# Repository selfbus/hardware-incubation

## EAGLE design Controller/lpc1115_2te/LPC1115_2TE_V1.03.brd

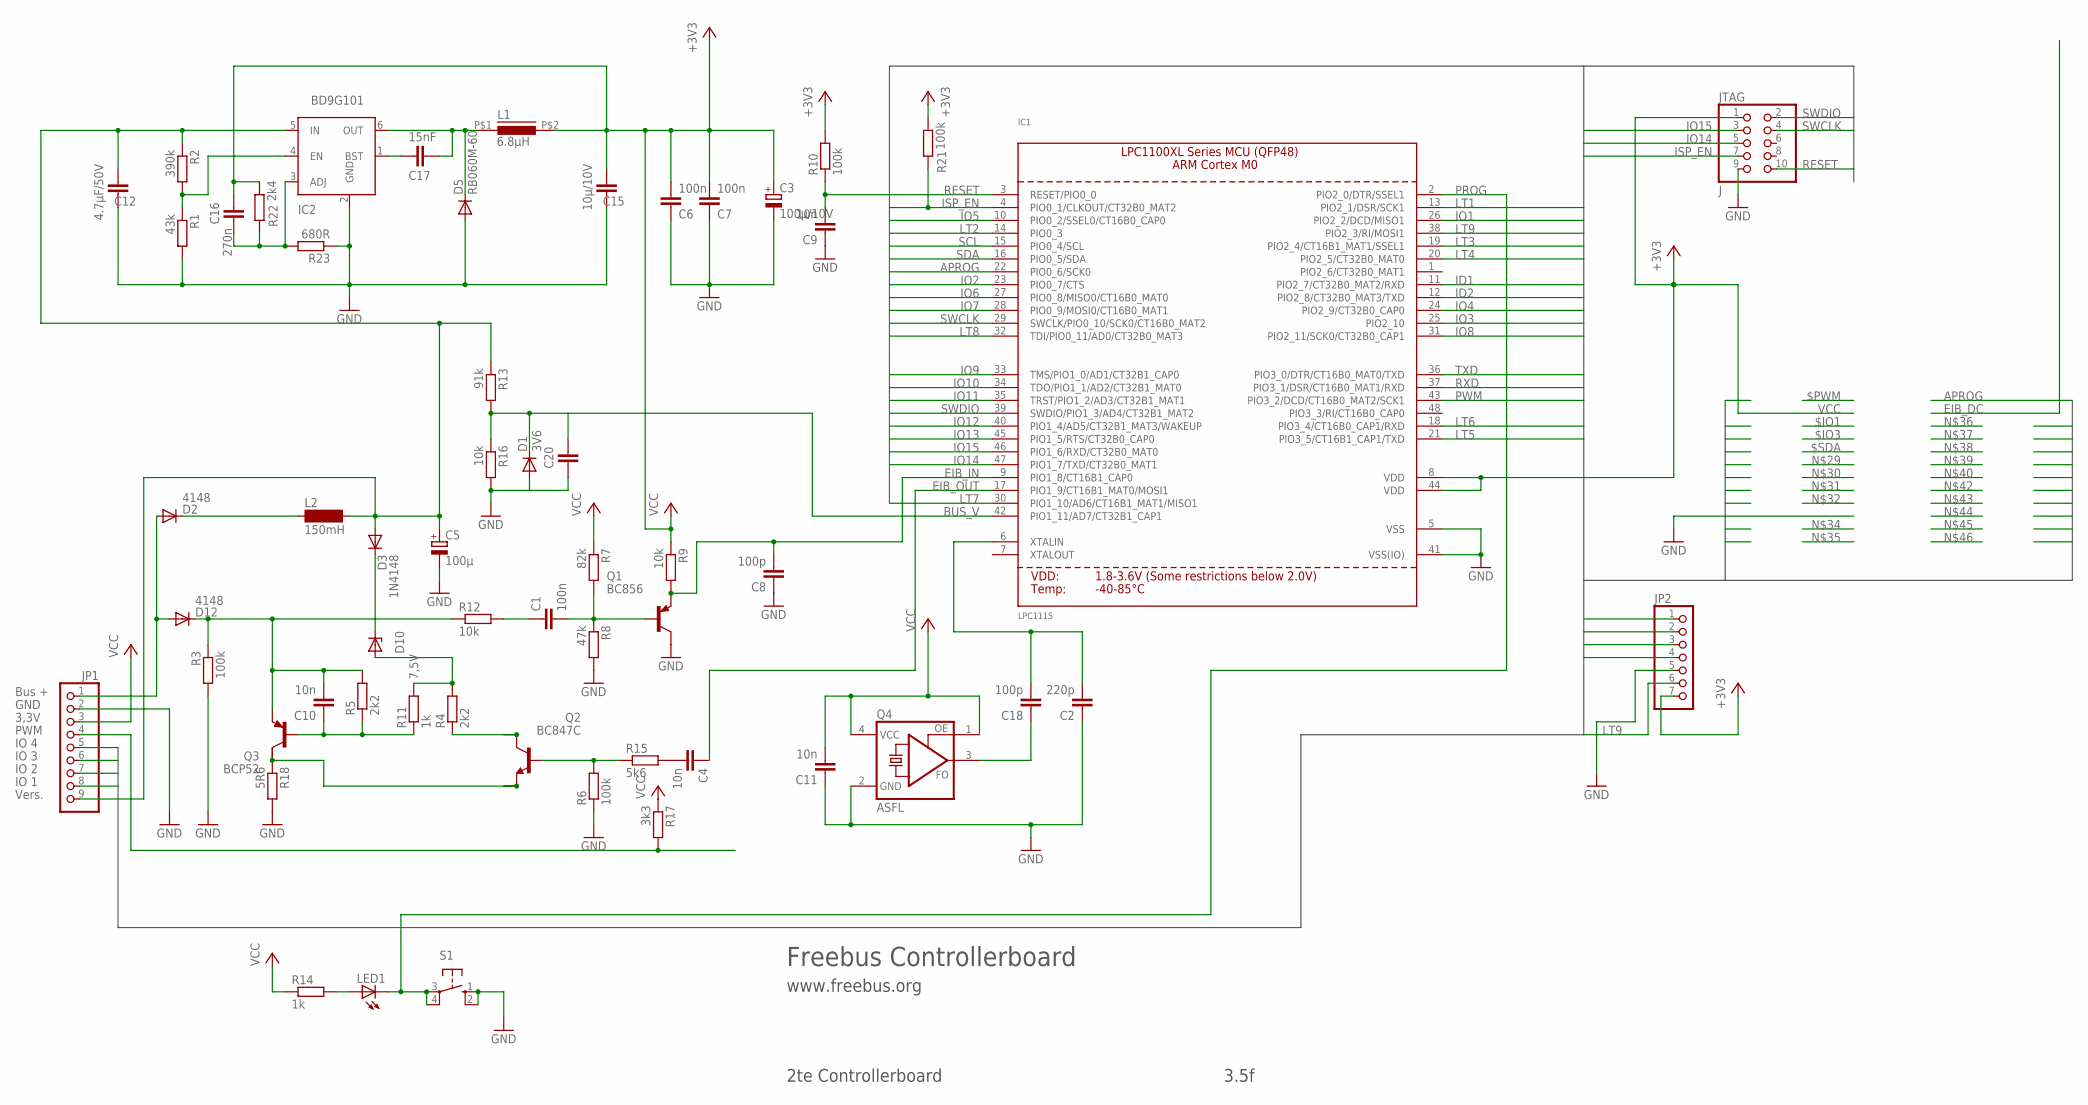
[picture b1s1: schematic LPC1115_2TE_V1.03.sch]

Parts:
C1, C6, C7: 100n; C1206
C2: 220p; C1206
C3: 100µ/10V; E2,5-5
C4, C10, C11: 10n; C1206
C5: 100µ; E3,5-8
C8: 100p; C1206K
C9: 10n; C1206K
C12: 4.7µF/50V; C1206K
C15: 10µ/10V; C1206K
C16: 270n; C1206
C17: 15nF; C1206
C18: 100p; C1206
C20: C-EUC1206; C1206
D1: 3V6; MINIMELF
D2, D12: 4148; MINIMELF
D3: 1N4148; MINIMELF
D5: RB060M-60; SOD123
D10: 7,5V; MINIMELF
IC1: LPC1115; LQFP48
IC2: BD9G101; SOT23-6
JP1: PINHD-1X9; 1X09
JP2: PINHD-1X7; 1X07
JTAG: J; 2X05M
L1: 6.8µH; PIS2812
L2: 150mH; BS11
LED1: LED3MM
Q1: BC856; SOT23-BEC
Q2: BC847C; SOT23
Q3: BCP52; SOT223
Q4: ASFL; ASF
R1: 43k; R1206
R2: 390k; R1206
R3, R6, R10, R21: 100k; R1206
R4, R5: 2k2; R1206
R7: 82k; R1206
R8: 47k; R1206
R9, R12, R16: 10k; R1206
R11, R14: 1k; R1206
R13: 91k; R1206
R15: 5k6; R1206
R17: 3k3; R1206
R18: 5R6; R1206
R22: 2k4; R1206
R23: 680R; R1206
S1: 10-XX; B3F-10XX

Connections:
APROG: IC1.22 (PIO0_6/SCK0), JP1.8
BASE: C1.2, Q1.B, R7.2, R8.1
BASE_SEND: Q2.1 (B), R6.2, R15.1
BUS_V: C20.2, D1.C, IC1.42 (PIO1_11/AD7/CT32B1_CAP1), R13.2, R16.1
EIB+: D2.A, D12.A, JP1.1
EIB_DC: C5.+, C12.2, D3.A, IC2.5 (IN), JP1.9, L2.2, R2.1, R13.1
EIB_IN: C8.2, IC1.9 (PIO1_8/CT16B1_CAP0), Q1.E, R9.2
EIB_OUT: C4.1, IC1.17 (PIO1_9/CT16B1_MAT0/MOSI1)
GND: C2.1, C3.-, C5.-, C6.1, C7.1, C8.1, C9.1, C11.1, C12.1, C15.1, C20.1, D1.A, D5.A, IC1.5 (VSS), IC1.41 (VSS(IO)), IC2.2 (GND), JP1.2, JP2.5, JTAG.9, Q1.C, Q4.2 (GND), R1.2, R3.2, R6.1, R8.2, R16.2, R18.2, R23.1, S1.1 (S), S1.2 (S1)
ID1: IC1.11 (PIO2_7/CT32B0_MAT2/RXD)
ID2: IC1.12 (PIO2_8/CT32B0_MAT3/TXD)
IO1: IC1.26 (PIO2_2/DCD/MISO1)
IO2: IC1.23 (PIO0_7/CTS)
IO3: IC1.25 (PIO2_10)
IO4: IC1.24 (PIO2_9/CT32B0_CAP0), JP1.5
IO5: IC1.10 (PIO0_2/SSEL0/CT16B0_CAP0)
IO6: IC1.27 (PIO0_8/MISO0/CT16B0_MAT0)
IO7: IC1.28 (PIO0_9/MOSI0/CT16B0_MAT1), JP1.7
IO8: IC1.31 (PIO2_11/SCK0/CT32B0_CAP1), JP1.6
IO9: IC1.33 (TMS/PIO1_0/AD1/CT32B1_CAP0)
IO10: IC1.34 (TDO/PIO1_1/AD2/CT32B1_MAT0)
IO11: IC1.35 (TRST/PIO1_2/AD3/CT32B1_MAT1)
IO12: IC1.40 (PIO1_4/AD5/CT32B1_MAT3/WAKEUP)
IO13: IC1.45 (PIO1_5/RTS/CT32B0_CAP0)
IO14: IC1.47 (PIO1_7/TXD/CT32B0_MAT1), JTAG.5
IO15: IC1.46 (PIO1_6/RXD/CT32B0_MAT0), JTAG.3
ISP_EN: IC1.4 (PIO0_1/CLKOUT/CT32B0_MAT2), JTAG.7, R21.1
I_SENSE: Q2.2 (E), Q3.2 (C), R18.1
LT1: IC1.13 (PIO2_1/DSR/SCK1)
LT2: IC1.14 (PIO0_3)
LT3: IC1.19 (PIO2_4/CT16B1_MAT1/SSEL1)
LT4: IC1.20 (PIO2_5/CT32B0_MAT0)
LT5: IC1.21 (PIO3_5/CT16B1_CAP1/TXD), JP2.1
LT6: IC1.18 (PIO3_4/CT16B0_CAP1/RXD), JP2.2
LT7: IC1.30 (PIO1_10/AD6/CT16B1_MAT1/MISO1), JP2.3
LT8: IC1.32 (TDI/PIO0_11/AD0/CT32B0_MAT3), JP2.4
LT9: IC1.38 (PIO2_3/RI/MOSI1), JP2.6
LX: C17.1, D5.C, IC2.6 (OUT), L1.P$1 (1)
unnamed: Q2.3 (C), R4.1
unnamed: C2.2, C18.2, IC1.6 (XTALIN)
unnamed: C10.2, D12.C, Q3.3 (E), R3.1, R5.2, R12.1
unnamed: C18.1, Q4.3 (FO)
unnamed: LED1.A, R14.2
unnamed: D2.C, L2.1
unnamed: D3.C, D10.C
unnamed: C1.1, R12.2
unnamed: C4.2, R15.2
unnamed: C17.2, IC2.1 (BST)
unnamed: IC2.4 (EN), R1.1, R2.2
unnamed: C16.1, IC2.3 (ADJ), R22.1, R23.2
unnamed: C10.1, Q3.1 (B), R5.1, R11.1
PROG: IC1.2 (PIO2_0/DTR/SSEL1), LED1.K (C), S1.3, S1.4 (P1)
PWM: IC1.43 (PIO3_2/DCD/CT16B0_MAT2/SCK1), JP1.4, R17.2
REFERENZ: D10.A, R4.2, R11.2
RESET: C9.2, IC1.3 (RESET/PIO0_0), JTAG.10, R10.1
RXD: IC1.37 (PIO3_1/DSR/CT16B0_MAT1/RXD)
SCL: IC1.15 (PIO0_4/SCL)
SDA: IC1.16 (PIO0_5/SDA)
SWCLK: IC1.29 (SWCLK/PIO0_10/SCK0/CT16B0_MAT2), JTAG.4
SWDIO: IC1.39 (SWDIO/PIO1_3/AD4/CT32B1_MAT2), JTAG.2
TXD: IC1.36 (PIO3_0/DTR/CT16B0_MAT0/TXD)
VCC: C3.+, C6.2, C7.2, C11.2, C15.2, C16.2, IC1.8 (VDD), IC1.44 (VDD), JP1.3, JP2.7, JTAG.1, L1.P$2 (2), Q4.1 (OE), Q4.4 (VCC), R7.1, R9.1, R10.2, R14.1, R17.1, R21.2, R22.2

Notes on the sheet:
Bus +
GND
3,3V
PWM
IO 1
IO 2
IO 3
IO 4
Vers.
Freebus Controllerboard
www.freebus.org
2te Controllerboard
3.5f

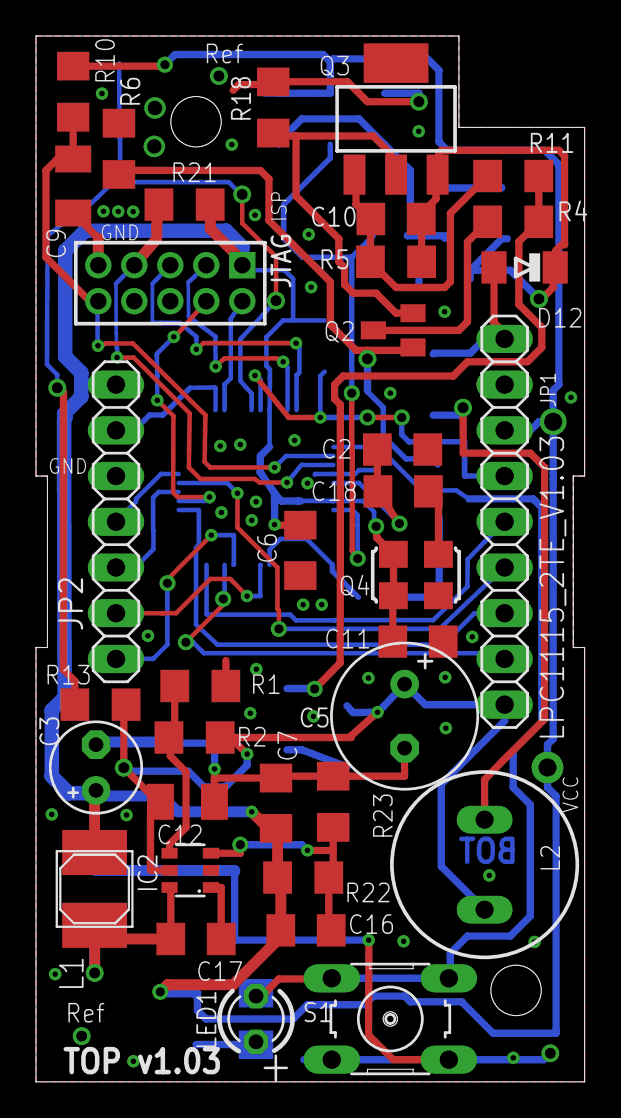
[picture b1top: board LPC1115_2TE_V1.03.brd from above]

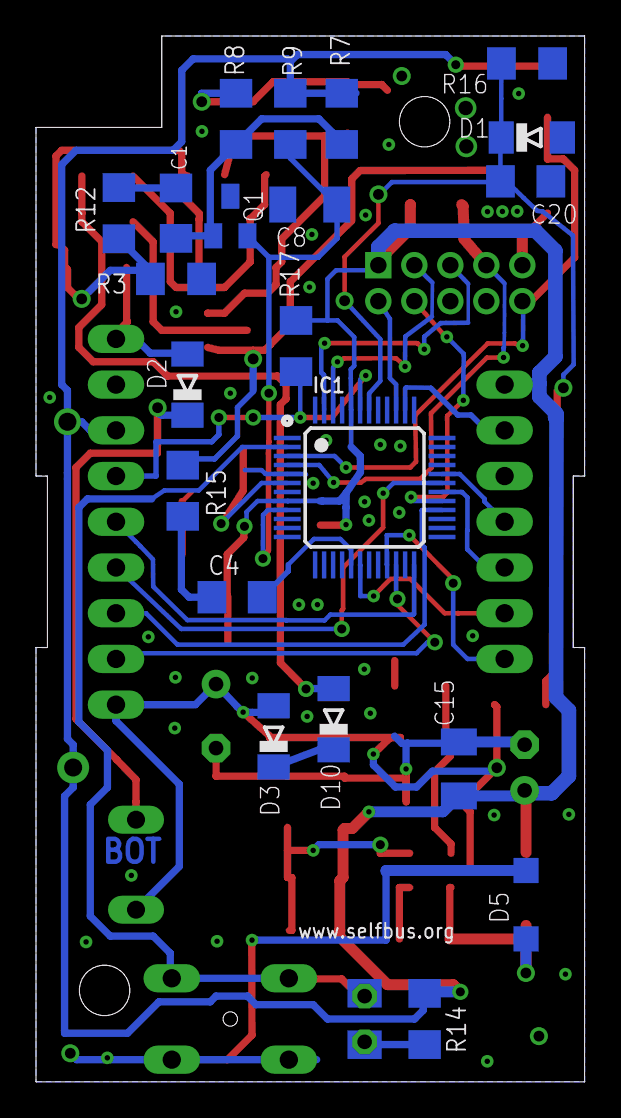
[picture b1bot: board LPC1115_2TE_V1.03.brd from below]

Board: 2 copper layers, 30.5 x 58.1 mm, 57 parts (21 on the bottom side), 42 nets.

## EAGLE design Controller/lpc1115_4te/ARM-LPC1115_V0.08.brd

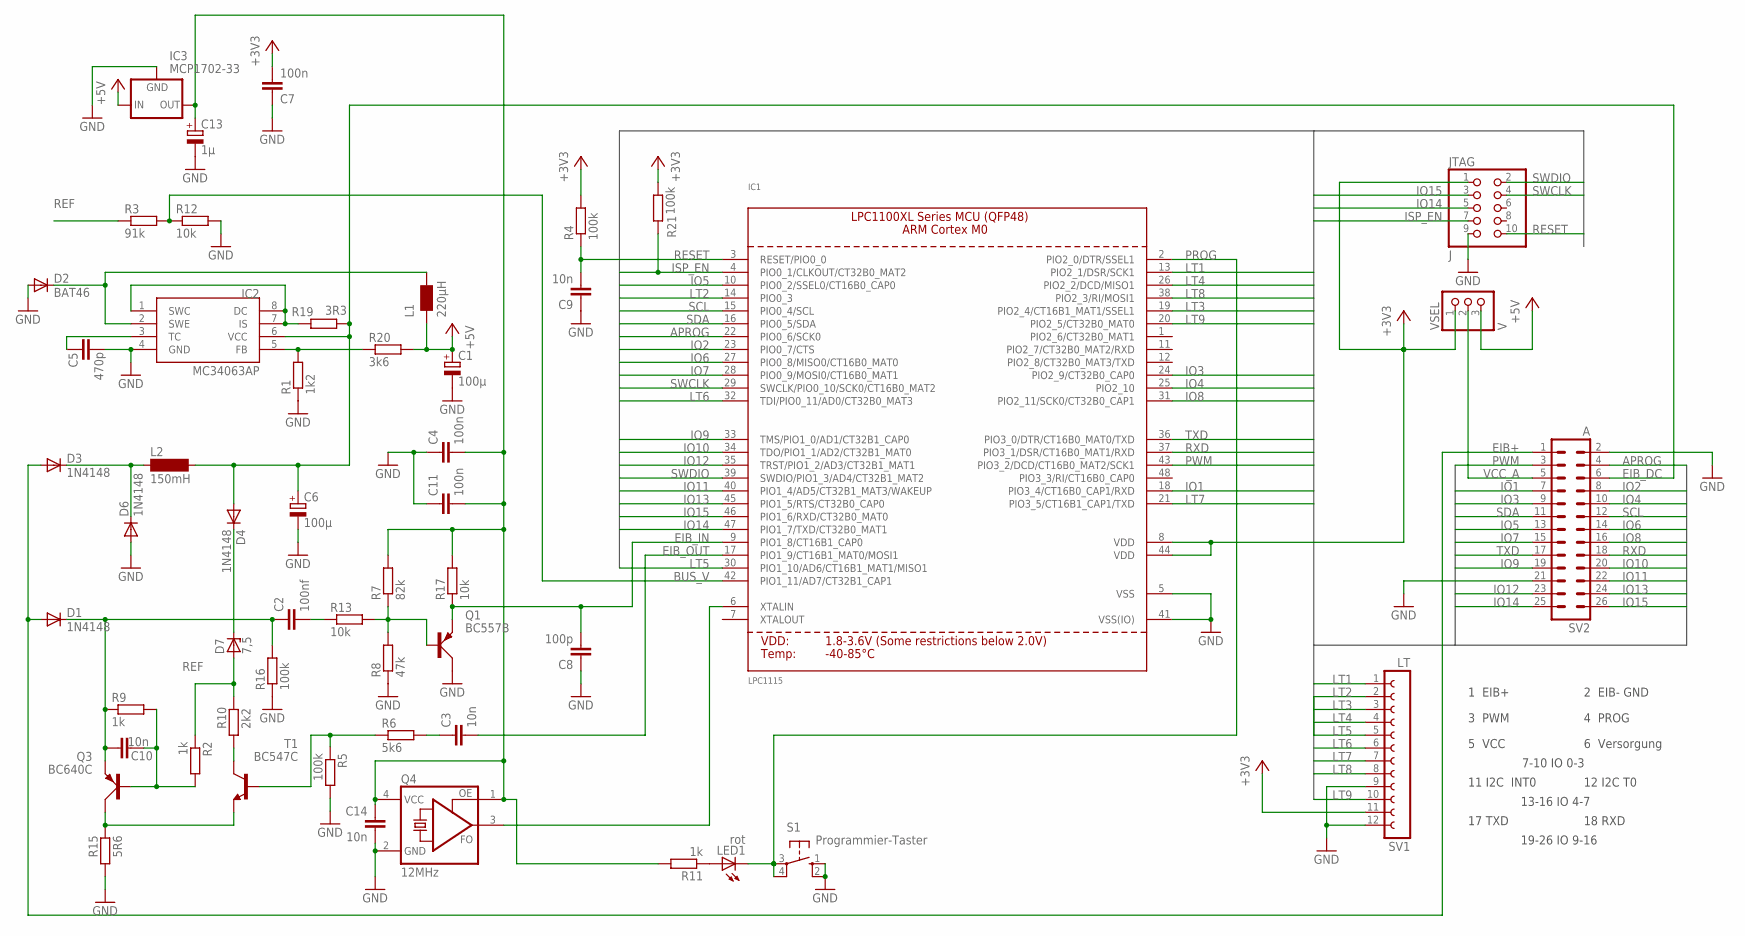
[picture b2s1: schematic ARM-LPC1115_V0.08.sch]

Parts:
C1, C6: 100µ; E5-8,5
C2: 100nf; C050-024X044
C3, C9, C10: 10n; C050-024X044
C4, C7, C11: 100n; C050-024X044
C5: 470p; C025-024X044
C8: 100p; C050-024X044
C13: 1µ; E2-4
C14: 10n; C1206
D1, D4: 1N4148; D-5
D2: BAT46; C1702-05
D3, D6: 1N4148; D-2.5
D7: 7,5; ZDIO-7.5
IC1: LPC1115; LQFP48
IC2: MC34063AP; DIL08
IC3: MCP1702-33; 79LXX
JTAG: J; 2X05M
L1: 220µH; L_RAD_D8RM5
L2: 150mH; SD12_1000
LED1: rot; LED3MM
Q1: BC557B; SOT54A
Q3: BC640C; SOT54D
Q4: 12MHz; ASF
R1: 1k2; 0207/10
R2, R9: 1k; 0204/7
R3: 91k; 0204/7
R4, R21: 100k; 0204/7
R5: 100k; 0207/10
R6: 5k6; 0204/7
R7: 82k; 0207/7
R8: 47k; 0207/7
R10: 2k2; 0204/7
R11: 1k; 0207/7
R12: 10k; 0204/7
R13, R17: 10k; 0207/7
R15: 5R6; 0207/10
R16: 100k; 0207/7
R19: 3R3; 0207/10
R20: 3k6; 0207/10
S1: Programmier-Taster; B3F-10XX
SV1: LT; FE12
SV2: A; ML26
T1: BC547C; TO92
VSEL: V; 1X03_ROUND

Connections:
APROG: IC1.22 (PIO0_6/SCK0), SV2.4
BUS_V: IC1.42 (PIO1_11/AD7/CT32B1_CAP1), R3.2, R12.1
DRAIN: C2.1, C10.1, D1.C, Q3.E, R9.1, R16.2
EIB+: D1.A, D3.A, SV2.1
EIB_DC: C6.+, D4.A, IC2.6 (VCC), L2.2, R19.2, SV2.6
EIB_IN: C8.2, IC1.9 (PIO1_8/CT16B1_CAP0), Q1.E, R17.1
EIB_OUT: C3.2, IC1.17 (PIO1_9/CT16B1_MAT0/MOSI1)
GND: C1.-, C4.1, C5.2, C6.-, C7.1, C8.1, C9.1, C11.1, C13.-, C14.2, D2.A, D6.A, IC1.5 (VSS), IC1.41 (VSS(IO)), IC2.4 (GND), IC3.GND, JTAG.9, Q1.C, Q4.2 (GND), R1.1, R5.2, R8.1, R12.2, R15.1, R16.1, S1.1 (S), S1.2 (S1), SV1.9, SV1.12, SV2.2, SV2.21
IO1: IC1.18 (PIO3_4/CT16B0_CAP1/RXD), SV2.7
IO2: IC1.23 (PIO0_7/CTS), SV2.8
IO3: IC1.24 (PIO2_9/CT32B0_CAP0), SV2.9
IO4: IC1.25 (PIO2_10), SV2.10
IO5: IC1.10 (PIO0_2/SSEL0/CT16B0_CAP0), SV2.13
IO6: IC1.27 (PIO0_8/MISO0/CT16B0_MAT0), SV2.14
IO7: IC1.28 (PIO0_9/MOSI0/CT16B0_MAT1), SV2.15
IO8: IC1.31 (PIO2_11/SCK0/CT32B0_CAP1), SV2.16
IO9: IC1.33 (TMS/PIO1_0/AD1/CT32B1_CAP0), SV2.19
IO10: IC1.34 (TDO/PIO1_1/AD2/CT32B1_MAT0), SV2.20
IO11: IC1.40 (PIO1_4/AD5/CT32B1_MAT3/WAKEUP), SV2.22
IO12: IC1.35 (TRST/PIO1_2/AD3/CT32B1_MAT1), SV2.23
IO13: IC1.45 (PIO1_5/RTS/CT32B0_CAP0), SV2.24
IO14: IC1.47 (PIO1_7/TXD/CT32B0_MAT1), JTAG.5, SV2.25
IO15: IC1.46 (PIO1_6/RXD/CT32B0_MAT0), JTAG.3, SV2.26
ISP_EN: IC1.4 (PIO0_1/CLKOUT/CT32B0_MAT2), JTAG.7, R21.1
LT1: IC1.13 (PIO2_1/DSR/SCK1), SV1.1
LT2: IC1.14 (PIO0_3), SV1.2
LT3: IC1.19 (PIO2_4/CT16B1_MAT1/SSEL1), SV1.3
LT4: IC1.26 (PIO2_2/DCD/MISO1), SV1.4
LT5: IC1.30 (PIO1_10/AD6/CT16B1_MAT1/MISO1), SV1.5
LT6: IC1.32 (TDI/PIO0_11/AD0/CT32B0_MAT3), SV1.6
LT7: IC1.21 (PIO3_5/CT16B1_CAP1/TXD), SV1.7
LT8: IC1.38 (PIO2_3/RI/MOSI1), SV1.8
LT9: IC1.20 (PIO2_5/CT32B0_MAT0), SV1.10
unnamed: C3.1, R6.2
unnamed: C2.2, R13.1
unnamed: IC2.5 (FB), R1.2, R20.1
unnamed: IC2.1 (SWC), IC2.7 (IS), IC2.8 (DC), R19.1
unnamed: R10.1, T1.3 (C)
unnamed: Q3.C, R15.2, T1.1 (E)
unnamed: D3.C, D6.C, L2.1
unnamed: D4.C, D7.C
unnamed: D2.C, IC2.2 (SWE), L1.1 (2)
unnamed: R5.1, R6.1, T1.2 (B)
unnamed: C5.1, IC2.3 (TC)
unnamed: Q1.B, R7.1, R8.2, R13.2
unnamed: C10.2, Q3.B, R2.2, R9.2
unnamed: IC1.6 (XTALIN), Q4.3 (FO)
unnamed: LED1.A, R11.1
PROG: IC1.2 (PIO2_0/DTR/SSEL1), LED1.K (C), S1.3, S1.4 (P1)
PWM: IC1.43 (PIO3_2/DCD/CT16B0_MAT2/SCK1), SV2.3
REF: D7.A, R2.1, R3.1, R10.2
RESET: C9.2, IC1.3 (RESET/PIO0_0), JTAG.10, R4.1
RXD: IC1.37 (PIO3_1/DSR/CT16B0_MAT1/RXD), SV2.18
SCL: IC1.15 (PIO0_4/SCL), SV2.12
SDA: IC1.16 (PIO0_5/SDA), SV2.11
SWCLK: IC1.29 (SWCLK/PIO0_10/SCK0/CT16B0_MAT2), JTAG.4
SWDIO: IC1.39 (SWDIO/PIO1_3/AD4/CT32B1_MAT2), JTAG.2
TXD: IC1.36 (PIO3_0/DTR/CT16B0_MAT0/TXD), SV2.17
VCC_3V3: C4.2, C7.2, C11.2, C13.+, C14.1, IC1.8 (VDD), IC1.44 (VDD), IC3.OUT, JTAG.1, Q4.1 (OE), Q4.4 (VCC), R4.2, R7.2, R11.2, R17.2, R21.2, SV1.11, VSEL.1
VCC_5V: C1.+, IC3.IN, L1.2 (1), R20.2, VSEL.3
VCC_A: SV2.5, VSEL.2

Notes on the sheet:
1 EIB+
2 EIB- GND
3 PWM
4 PROG
5 VCC
6 Versorgung
7-10 IO 0-3
11 I2C INT0
12 I2C T0
13-16 IO 4-7
17 TXD
18 RXD
19-26 IO 9-16

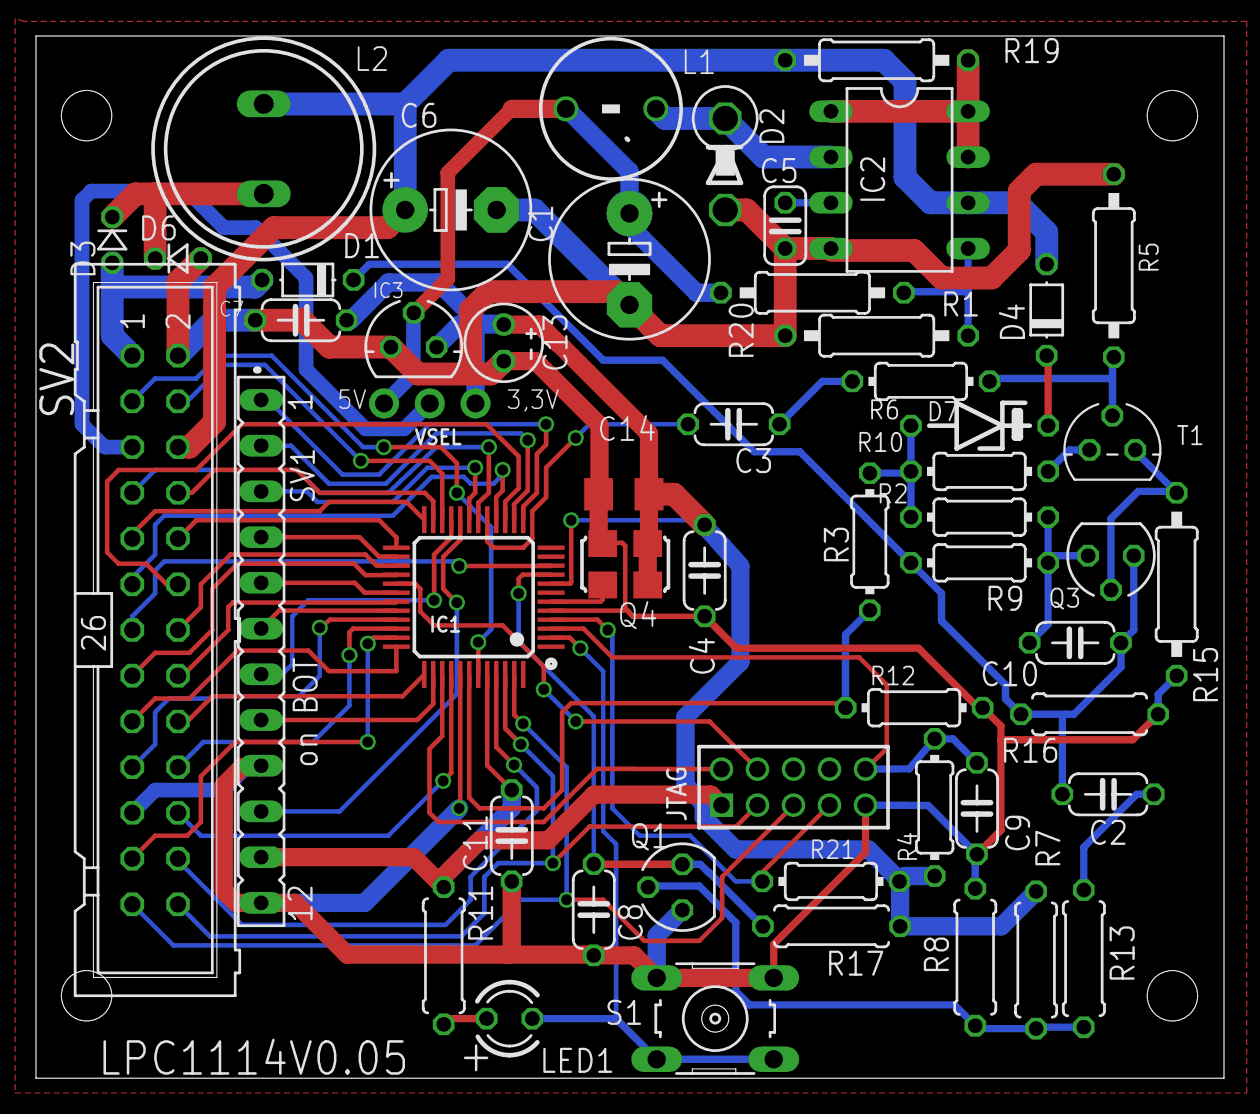
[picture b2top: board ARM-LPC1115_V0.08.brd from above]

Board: 2 copper layers, 66.0 x 57.9 mm, 53 parts (0 on the bottom side), 61 nets.

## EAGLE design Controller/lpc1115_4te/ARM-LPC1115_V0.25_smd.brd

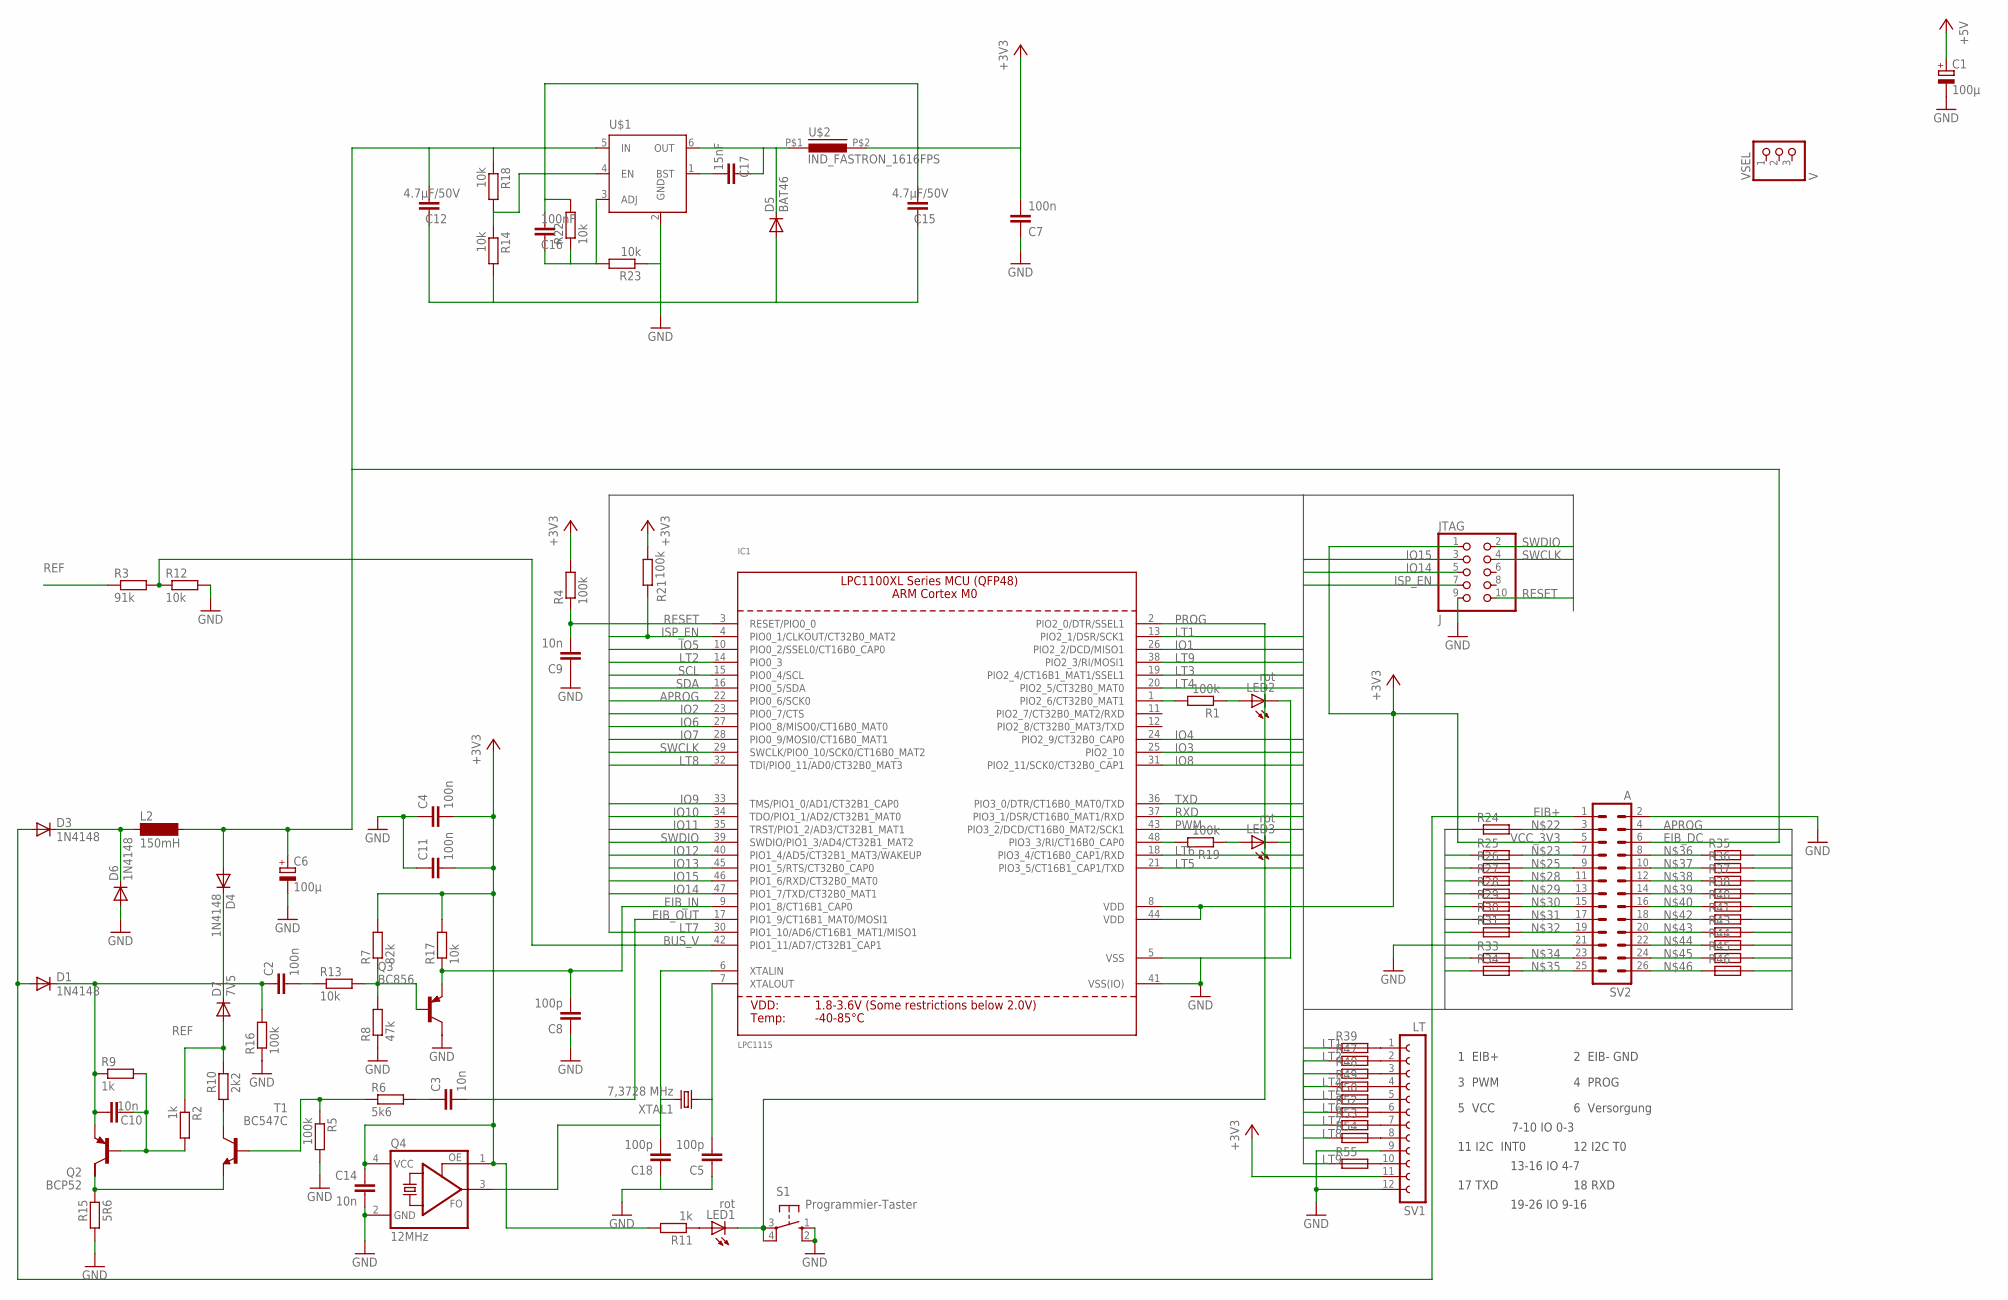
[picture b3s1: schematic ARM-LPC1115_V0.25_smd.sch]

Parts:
C1, C6: 100µ; E5-8,5
C2: 100n; C1206K
C3, C9, C10: 10n; C1206K
C4, C7, C11: 100n; C1206
C5, C18: 100p; C0603
C8: 100p; C1206K
C12, C15: 4.7µF/50V; C1206K
C14: 10n; C1206
C16: 100nF; C1206
C17: 15nF; C1206
D1, D3, D4, D6: 1N4148; MINIMELF
D5: BAT46; DO214AC
D7: 7V5; MINIMELF
IC1: LPC1115; LQFP48
JTAG: J; 2X05M
L2: 150mH; SD12_1000
LED1: rot; LED3MM
LED2, LED3: rot; 1206
Q2: BCP52; SOT223
Q3: BC856; SOT23-BEC
Q4: 12MHz; ASF
R1, R4, R5, R16, R19, R21: 100k; R1206
R2, R9, R11: 1k; R1206
R3: 91k; R1206
R6: 5k6; R1206
R7: 82k; R1206
R8: 47k; R1206
R10: 2k2; R1206
R12, R13, R14, R17, R18, R22, R23: 10k; R1206
R15: 5R6; R1206
R24, R25, R26, R27, R28, R29, R30, R31, R33, R34, R35, R36, R37, R38, R39, R40, R41, R43, R44, R45, R46, R47, R48, R49, R50, R52, R53, R54, R55: R-EU_BRIDGER0603; R0603_BRIDGE
S1: Programmier-Taster; B3F-10XX
SV1: LT; FE12
SV2: A; ML26
T1: BC547C; SOT23
U$1: BD9G101GBD9G101G-SOT23-6; SOT23-6
U$2: IND_FASTRON_1616FPS; PIS2812
VSEL: V; 1X03_ROUND
XTAL1: 7,3728 MHz; HC49/S

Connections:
+5V: C1.+
APROG: IC1.22 (PIO0_6/SCK0), SV2.4
BUS_V: IC1.42 (PIO1_11/AD7/CT32B1_CAP1), R3.2, R12.1
DRAIN: C2.1, C10.1, D1.C, Q2.3 (E), R9.1, R16.2
EIB+: D1.A, D3.A, SV2.1
EIB_DC: C6.+, C12.2, D4.A, L2.2, R18.1, SV2.6, U$1.5 (IN)
EIB_IN: C8.2, IC1.9 (PIO1_8/CT16B1_CAP0), Q3.E, R17.1
EIB_OUT: C3.2, IC1.17 (PIO1_9/CT16B1_MAT0/MOSI1)
GND: C1.-, C4.1, C5.1, C6.-, C7.1, C8.1, C9.1, C11.1, C12.1, C14.2, C15.1, C18.1, D5.A, D6.A, IC1.5 (VSS), IC1.41 (VSS(IO)), JTAG.9, LED2.C, LED3.C, Q3.C, Q4.2 (GND), R5.2, R8.1, R12.2, R14.2, R15.1, R16.1, R23.1, S1.1 (S), S1.2 (S1), SV1.9, SV1.12, SV2.2, SV2.21, U$1.2 (GND)
IO1: IC1.26 (PIO2_2/DCD/MISO1), R25.1
IO2: IC1.23 (PIO0_7/CTS), R35.2
IO3: IC1.25 (PIO2_10), R26.1
IO4: IC1.24 (PIO2_9/CT32B0_CAP0), R36.2
IO5: IC1.10 (PIO0_2/SSEL0/CT16B0_CAP0), R28.1
IO6: IC1.27 (PIO0_8/MISO0/CT16B0_MAT0), R38.2
IO7: IC1.28 (PIO0_9/MOSI0/CT16B0_MAT1), R29.1
IO8: IC1.31 (PIO2_11/SCK0/CT32B0_CAP1), R40.2
IO9: IC1.33 (TMS/PIO1_0/AD1/CT32B1_CAP0), R31.1
IO10: IC1.34 (TDO/PIO1_1/AD2/CT32B1_MAT0), R43.2
IO11: IC1.35 (TRST/PIO1_2/AD3/CT32B1_MAT1), R44.2
IO12: IC1.40 (PIO1_4/AD5/CT32B1_MAT3/WAKEUP), R33.1
IO13: IC1.45 (PIO1_5/RTS/CT32B0_CAP0), R45.2
IO14: IC1.47 (PIO1_7/TXD/CT32B0_MAT1), JTAG.5, R34.1
IO15: IC1.46 (PIO1_6/RXD/CT32B0_MAT0), JTAG.3, R46.2
ISP_EN: IC1.4 (PIO0_1/CLKOUT/CT32B0_MAT2), JTAG.7, R21.1
LT1: IC1.13 (PIO2_1/DSR/SCK1), R39.1
LT2: IC1.14 (PIO0_3), R47.1
LT3: IC1.19 (PIO2_4/CT16B1_MAT1/SSEL1), R48.1
LT4: IC1.20 (PIO2_5/CT32B0_MAT0), R49.1
LT5: IC1.21 (PIO3_5/CT16B1_CAP1/TXD), R50.1
LT6: IC1.18 (PIO3_4/CT16B0_CAP1/RXD), R52.1
LT7: IC1.30 (PIO1_10/AD6/CT16B1_MAT1/MISO1), R53.1
LT8: IC1.32 (TDI/PIO0_11/AD0/CT32B0_MAT3), R54.1
LT9: IC1.38 (PIO2_3/RI/MOSI1), R55.1
LX: C17.1, D5.C, U$1.6 (OUT), U$2.P$1 (1)
unnamed: C3.1, R6.2
unnamed: C2.2, R13.1
unnamed: C5.2, IC1.7 (XTALOUT), XTAL1.1
unnamed: IC1.1 (PIO2_6/CT32B0_MAT1), R1.2
unnamed: IC1.48 (PIO3_3/RI/CT16B0_CAP0), R19.2
unnamed: R10.1, T1.3 (C)
unnamed: Q2.2 (C), R15.2, T1.2 (E)
unnamed: D3.C, D6.C, L2.1
unnamed: D4.C, D7.C
unnamed: LED2.A, R1.1
unnamed: LED3.A, R19.1
unnamed: R5.1, R6.1, T1.1 (B)
unnamed: Q3.B, R7.1, R8.2, R13.2
unnamed: C10.2, Q2.1 (B), R2.2, R9.2
unnamed: C18.2, IC1.6 (XTALIN), Q4.3 (FO), XTAL1.2
unnamed: C17.2, U$1.1 (BST)
unnamed: R14.1, R18.2, U$1.4 (EN)
unnamed: R24.2, SV2.3
unnamed: R25.2, SV2.7
unnamed: C16.1, R22.1, R23.2, U$1.3 (ADJ)
unnamed: R26.2, SV2.9
unnamed: R27.2, SV2.11
unnamed: R28.2, SV2.13
unnamed: R29.2, SV2.15
unnamed: R30.2, SV2.17
unnamed: R31.2, SV2.19
unnamed: R33.2, SV2.23
unnamed: R34.2, SV2.25
unnamed: R35.1, SV2.8
unnamed: R36.1, SV2.10
unnamed: R37.1, SV2.12
unnamed: R38.1, SV2.14
unnamed: R40.1, SV2.16
unnamed: LED1.A, R11.1
unnamed: R41.1, SV2.18
unnamed: R43.1, SV2.20
unnamed: R44.1, SV2.22
unnamed: R45.1, SV2.24
unnamed: R46.1, SV2.26
unnamed: R39.2, SV1.1
unnamed: R47.2, SV1.2
unnamed: R48.2, SV1.3
unnamed: R49.2, SV1.4
unnamed: R50.2, SV1.5
unnamed: R52.2, SV1.6
unnamed: R53.2, SV1.7
unnamed: R54.2, SV1.8
unnamed: R55.2, SV1.10
PROG: IC1.2 (PIO2_0/DTR/SSEL1), LED1.K (C), S1.3, S1.4 (P1)
PWM: IC1.43 (PIO3_2/DCD/CT16B0_MAT2/SCK1), R24.1
REF: D7.A, R2.1, R3.1, R10.2
RESET: C9.2, IC1.3 (RESET/PIO0_0), JTAG.10, R4.1
RXD: IC1.37 (PIO3_1/DSR/CT16B0_MAT1/RXD), R41.2
SCL: IC1.15 (PIO0_4/SCL), R37.2
SDA: IC1.16 (PIO0_5/SDA), R27.1
SWCLK: IC1.29 (SWCLK/PIO0_10/SCK0/CT16B0_MAT2), JTAG.4
SWDIO: IC1.39 (SWDIO/PIO1_3/AD4/CT32B1_MAT2), JTAG.2
TXD: IC1.36 (PIO3_0/DTR/CT16B0_MAT0/TXD), R30.1
VCC_3V3: C4.2, C7.2, C11.2, C14.1, C15.2, C16.2, IC1.8 (VDD), IC1.44 (VDD), JTAG.1, Q4.1 (OE), Q4.4 (VCC), R4.2, R7.2, R11.2, R17.2, R21.2, R22.2, SV1.11, SV2.5, U$2.P$2 (2)

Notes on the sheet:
1 EIB+
2 EIB- GND
3 PWM
4 PROG
5 VCC
6 Versorgung
7-10 IO 0-3
11 I2C INT0
12 I2C T0
13-16 IO 4-7
17 TXD
18 RXD
19-26 IO 9-16

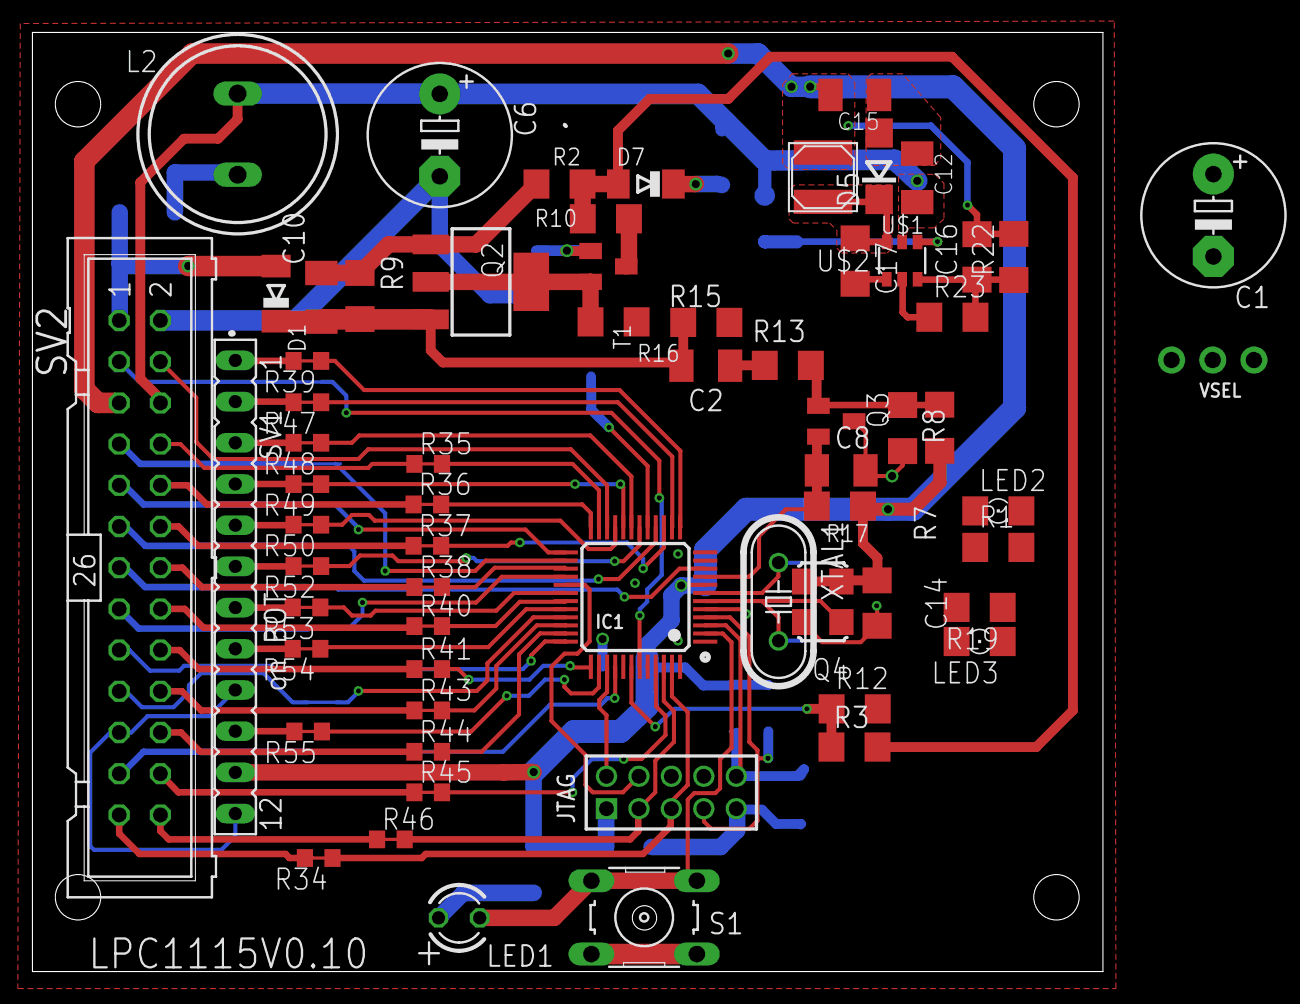
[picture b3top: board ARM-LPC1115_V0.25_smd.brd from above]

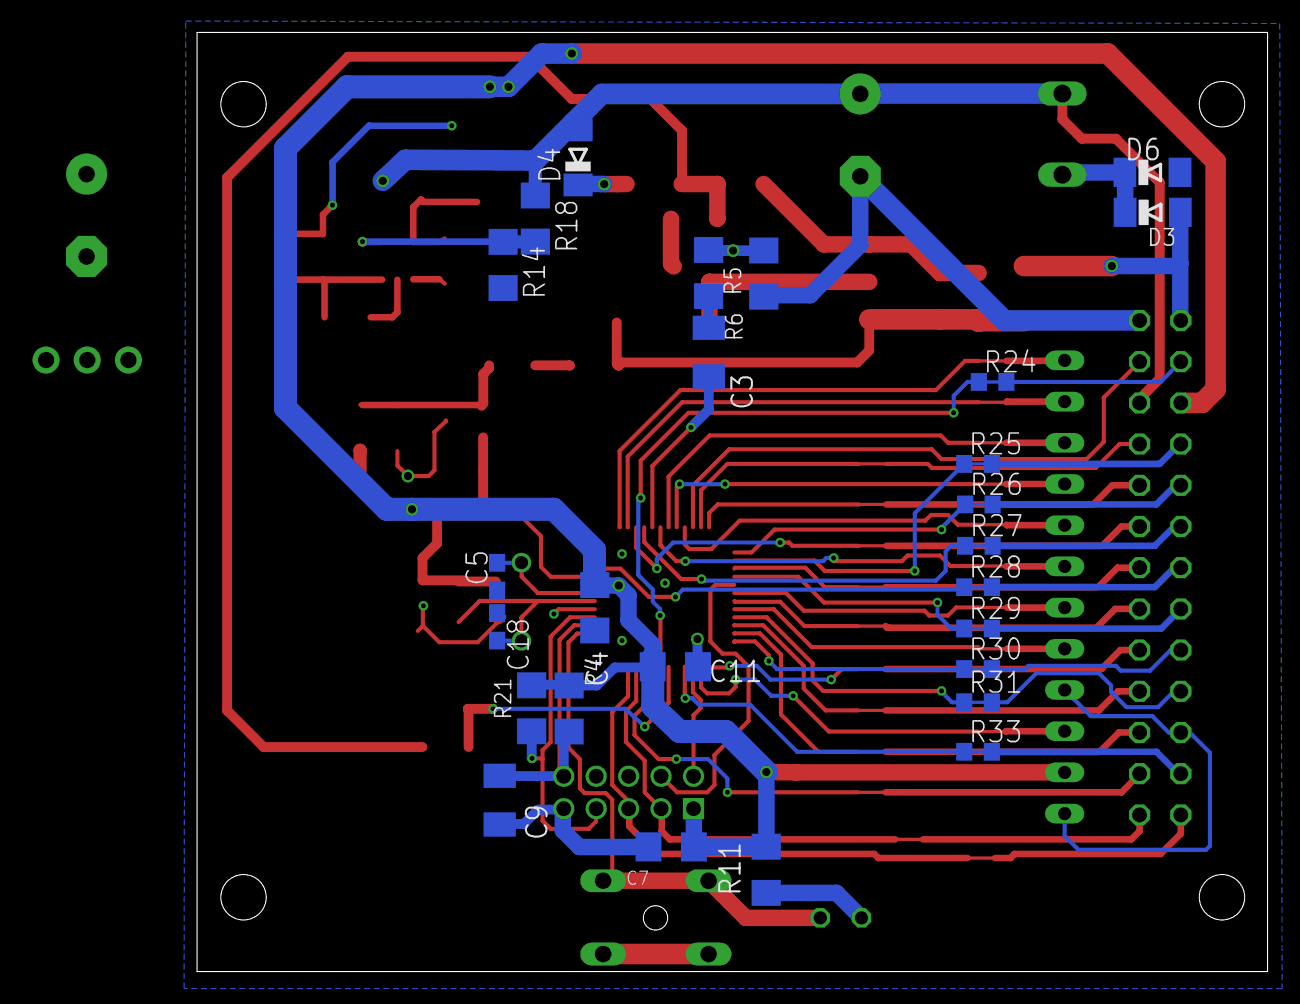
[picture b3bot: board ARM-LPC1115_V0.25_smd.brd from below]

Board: 2 copper layers, 66.0 x 57.9 mm, 91 parts (26 on the bottom side), 93 nets.

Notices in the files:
parts and their libraries:
microbuilder: This work is placed in the public domain, and may be freely used for commercial and non-commercial work with the following conditions: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
